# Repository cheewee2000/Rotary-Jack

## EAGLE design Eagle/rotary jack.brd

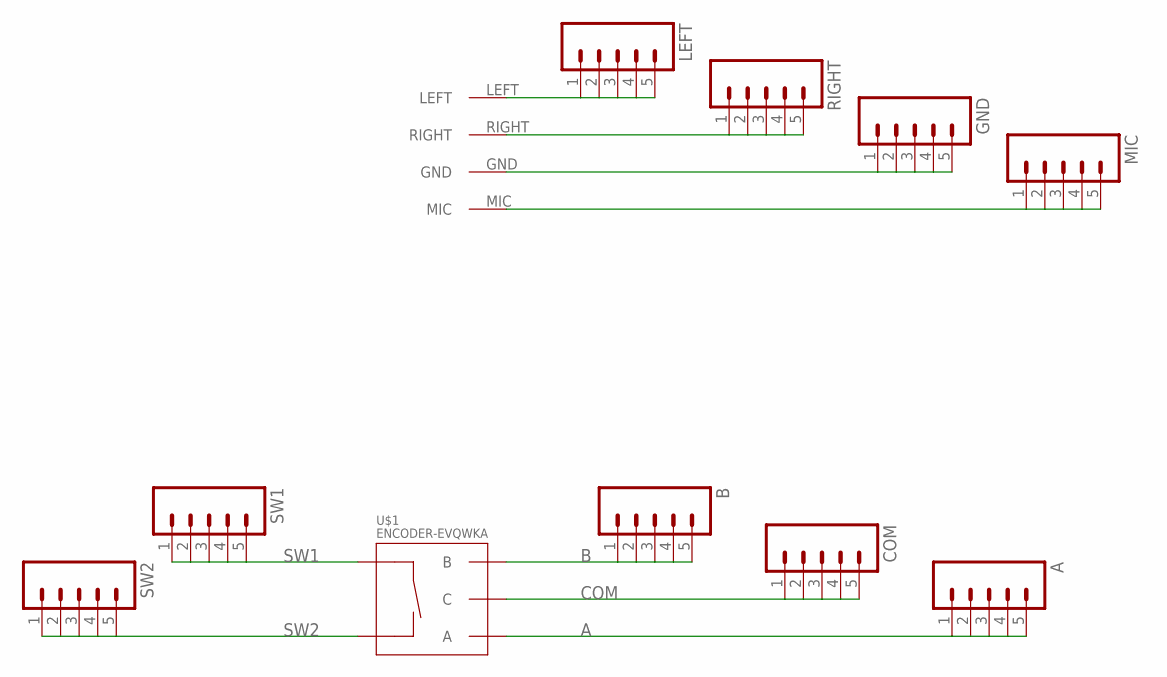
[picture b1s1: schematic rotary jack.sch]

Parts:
A: M05NO_SILK; 1X05_NO_SILK
B: M05NO_SILK; 1X05_NO_SILK
COM: M05NO_SILK; 1X05_NO_SILK
GND: M05NO_SILK; 1X05_NO_SILK
LEFT: M05NO_SILK; 1X05_NO_SILK
MIC: M05NO_SILK; 1X05_NO_SILK
RIGHT: M05NO_SILK; 1X05_NO_SILK
SW1, SW2: M05NO_SILK; 1X05_NO_SILK
U$1: ENCODER-EVQWKA
U$2: MALE-HEADPHONEMIC; MALEHEADPHONE

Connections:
A: A.1, A.2, A.3, A.4, A.5, U$1.A
B: B.1, B.2, B.3, B.4, B.5, U$1.B
COM: COM.1, COM.2, COM.3, COM.4, COM.5, U$1.COM (C)
GND: GND.1, GND.2, GND.3, GND.4, GND.5, U$2.GND
unnamed: LEFT.1, LEFT.2, LEFT.3, LEFT.4, LEFT.5, U$2.LEFT
unnamed: RIGHT.1, RIGHT.2, RIGHT.3, RIGHT.4, RIGHT.5, U$2.RIGHT
unnamed: MIC.1, MIC.2, MIC.3, MIC.4, MIC.5, U$2.MIC
SW1: SW1.1, SW1.2, SW1.3, SW1.4, SW1.5, U$1.SW1 (SW+)
SW2: SW2.1, SW2.2, SW2.3, SW2.4, SW2.5, U$1.SW2 (SW-)

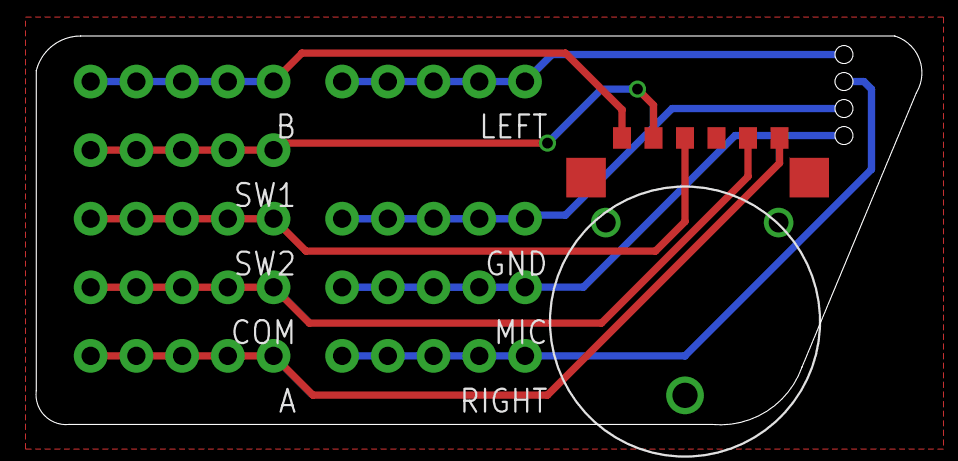
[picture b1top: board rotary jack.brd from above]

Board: 2 copper layers, 49.2 x 21.6 mm, 11 parts (1 on the bottom side), 9 nets.

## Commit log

2015-05-10 init
2015-07-21 too much to summarize.
2015-07-21 naming.

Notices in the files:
parts and their libraries:
SparkFun-Connectors: Licensing: CC v3.0 Share-Alike You are welcome to use this library for commercial purposes.
